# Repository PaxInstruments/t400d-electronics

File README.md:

# t400d-electronics
The T400D is the development tool based on the T400.

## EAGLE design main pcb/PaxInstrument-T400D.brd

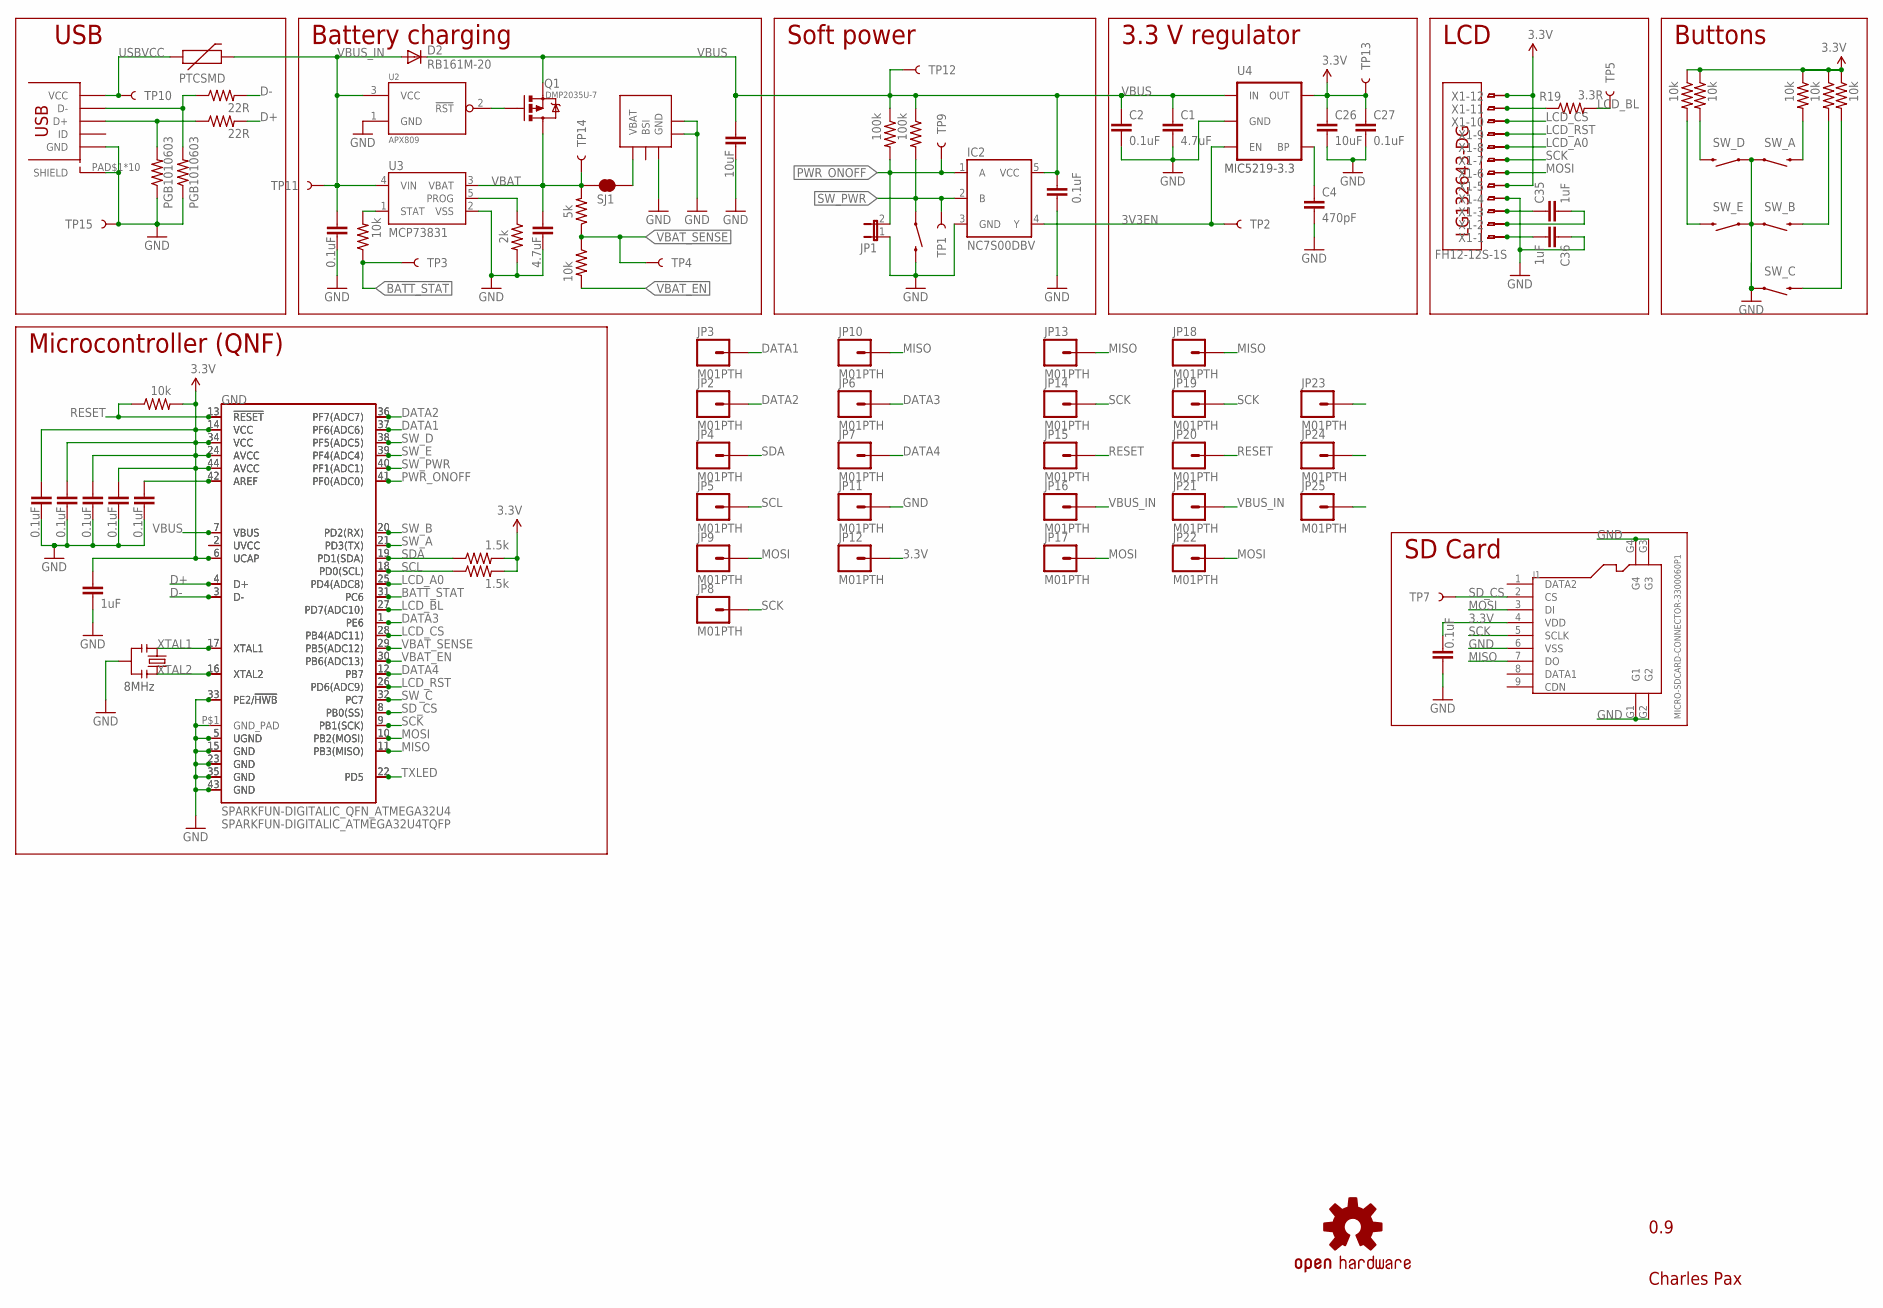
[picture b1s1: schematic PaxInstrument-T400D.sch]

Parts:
C1, C9: 4.7uF; SPARKFUN-CAPACITORS_0603-CAP; MPN GRM188R60J475KE19D
C2, C3, C5, C6, C21, C27, C28, C32, C33, C34: 0.1uF; SPARKFUN-CAPACITORS_0603-CAP; MPN CL10B104KO8NNNC
C4: 470pF; SPARKFUN-CAPACITORS_0603-CAP; MPN C1608X5R1A474K080AA
C12, C26: 10uF; SPARKFUN-CAPACITORS_0603-CAP; MPN JMK107ABJ106MAHT
C19, C35, C36: 1uF; SPARKFUN-CAPACITORS_0603-CAP; MPN LMK107B7105KA-T
D2: RB161M-20; SOD123; MPN B340A-13-F
F1: PTCSMD; PTC-1206; MPN MF-NSMF050-2
GND: SPARKFUN-DIGITALIC_QFN_ATMEGA32U4; SPARKFUN-DIGITALIC_SPARKFUN-DIGITALIC_QFN-44
IC2: NC7S00DBV; CHARLESPAX_SOT23-5
J1: MICRO-SDCARD-CONNECTOR-3300060P1; 9P-SMD-W-RING
JP1: JUMPER-2SMD-NO; SJ_2S-NO
JP2, JP3, JP4, JP5, JP6, JP7, JP8, JP9, JP10, JP11, JP12, JP13, JP14, JP15, JP16, JP17, JP18, JP19, JP20, JP21, JP22, JP23, JP24, JP25: M01PTH; 1X01
LOGO1: OSHW-LOGOS; OSHW-LOGO-S; MPN N/A
Q1: DMP2035U-7; SOT23
R3: 2k; SPARKFUN-RESISTORS_0603-RES; MPN ESR03EZPJ202
R4, R8, R11, R12, R15, R16, R17, R24: 10k; SPARKFUN-RESISTORS_0603-RES; MPN RC1608J103CS
R6, R7: 100k; SPARKFUN-RESISTORS_0603-RES; MPN RC1608J103CS
R9, R10: 22R; SPARKFUN-RESISTORS_0603-RES; MPN RC0603JR-0722RL
R13, R14: 1.5k; SPARKFUN-RESISTORS_0603-RES; MPN RC0603JR-071K5L
R19: 3.3R; SPARKFUN-RESISTORS_0603-RES
R20: 5k; SPARKFUN-RESISTORS_0603-RES; MPN RC1608J103CS
S1, S2, S3, S4, S5, S6: SWITCH-MOMENTARY-2SMD; TACTILE_SWITCH_SMD
SJ1: JUMPER-PAD-2-NC_BY_TRACE; PAD-JUMPER-2-NC_BY_TRACE_YES_SILK
TP1: SW_PWR; TP_15TH; MPN N/A
TP2: 3V3_EN; TP_15TH; MPN N/A
TP3: BATT_STAT; TP_15TH; MPN N/A
TP4: VBAT_SENSE; TP_15TH; MPN N/A
TP5: LCD_BL; TP_15TH; MPN N/A
TP7: SD_CS; TP_15TH; MPN N/A
TP9: PWR_ON/OFF; TP_15TH; MPN N/A
TP10: TEST-POINTTP_15TH_THRU; TP_15TH; MPN N/A
TP11: VBUS_IN; TP_15TH; MPN N/A
TP12: VBUS; TP_15TH; MPN N/A
TP13: 3.3V; TP_15TH; MPN N/A
TP14: VBAT; TP_15TH; MPN N/A
TP15: GND; TP_15TH
U2: APX809; SOT23
U3: MCP73831; SOT23-5; MPN MCP73831T-2DCI/OT
U4: MIC5219-3.3V; SOT23-5; MPN MIC5219-3.3YM5 TR
U$1: USB_MICROSMT+THRUHULE; USB_MICRO_THRUHOLE; MPN 10118194-0001LF
U$2: BL-5C-CONNECTOR
U$3: SPARKFUN-DIGITALIC_ATMEGA32U4TQFP; SPARKFUN-DIGITALIC_SPARKFUN-DIGITALIC_TQFP44
U$5: LG132643-DG; MPN LG132643-DW
X1: FH12-12S-1S; FH12-12S-1SH
X2: FH12-12S-0.5SH
Y1: RESONATORSMD; RESONATOR-SMD; MPN CSTCE8M00G52-R0
Z1, Z2: PGB1010603; SPARKFUN-RESISTORS_0603-RES; MPN PGB1010603NRHF

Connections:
3.3V: C5.1, C19.1, C21.2, C26.1, C27.1, C32.1, C33.1, C34.1, GND.6 (UCAP), GND.14 (VCC), GND.24 (AVCC), GND.34 (VCC), GND.44 (AVCC), J1.4 (VDD), JP12.1, R4.2, R8.1, R11.1, R12.1, R13.2, R14.2, R15.1, R16.1, TP13.P$1, U4.5 (OUT), U$3.6 (UCAP), U$3.14 (VCC), U$3.24 (AVCC), U$3.34 (VCC), U$3.44 (AVCC), X1.5, X1.12, X2.5, X2.12
3V3EN: IC2.4 (Y), TP2.P$1, U4.3 (EN)
BATT_STAT: GND.31 (PC6), R17.1, TP3.P$1, U$3.31 (PC6)
D+: GND.4 (D+), R9.2, U$3.4 (D+)
D-: GND.3 (D-), R10.2, U$3.3 (D-)
DATA1: GND.37 (PF6(ADC6)), JP3.1, U$3.37 (PF6(ADC6))
DATA2: GND.36 (PF7(ADC7)), JP2.1, U$3.36 (PF7(ADC7))
DATA3: GND.1 (PE6), JP6.1, U$3.1 (PE6)
DATA4: GND.12 (PB7), JP7.1, U$3.12 (PB7)
GND: C1.2, C2.2, C3.2, C4.2, C5.2, C6.2, C9.2, C12.2, C19.2, C21.1, C26.2, C27.2, C28.2, C32.2, C33.2, C34.2, C36.1, GND.5 (UGND), GND.15 (GND), GND.23 (GND), GND.33 (PE2/!HWB), GND.35 (GND), GND.43 (GND), GND.P$1 (GND_PAD), IC2.3 (GND), J1.6 (VSS), J1.G1, J1.G2, J1.G3, J1.G4, JP1.1, JP11.1, R3.2, S1.1, S2.1, S3.1, S4.1, S5.1, S6.3 (2), TP15.P$1, U2.1 (GND), U3.2 (VSS), U4.2 (GND), U$1.PAD$1 (SHIELD), U$1.PAD$2 (SHIELD), U$1.PAD$3 (SHIELD), U$1.PAD$4 (SHIELD), U$1.PAD$5 (SHIELD), U$1.PAD$6 (SHIELD), U$1.PAD$7 (SHIELD), U$1.PAD$8 (SHIELD), U$1.PAD$9 (SHIELD), U$1.PAD$10 (SHIELD), U$1.PIN$5 (GND), U$2.P$3 (GND), U$2.P$4, U$2.P$5, U$3.5 (UGND), U$3.15 (GND), U$3.23 (GND), U$3.33 (PE2/!HWB), U$3.35 (GND), U$3.43 (GND), X1.4, X2.4, Y1.2, Z1.1, Z2.1
LCD_A0: GND.25 (PD4(ADC8)), U$3.25 (PD4(ADC8)), X1.8, X2.8
LCD_BL: GND.27 (PD7(ADC10)), R19.2, TP5.P$1, U$3.27 (PD7(ADC10))
LCD_CS: GND.28 (PB4(ADC11)), U$3.28 (PB4(ADC11)), X1.10, X2.10
LCD_RST: GND.26 (PD6(ADC9)), U$3.26 (PD6(ADC9)), X1.9, X2.9
MISO: GND.11 (PB3(MISO)), J1.7 (DO), JP10.1, JP13.1, JP18.1, U$3.11 (PB3(MISO))
MOSI: GND.10 (PB2(MOSI)), J1.3 (DI), JP9.1, JP17.1, JP22.1, U$3.10 (PB2(MOSI)), X1.6, X2.6
MOSI2: JP25.1
unnamed: C4.1, U4.4 (BP)
unnamed: R17.2, U3.1 (STAT)
unnamed: R19.1, X1.11, X2.11
unnamed: R3.1, U3.5 (PROG)
unnamed: SJ1.2, U$2.P$1 (VBAT)
unnamed: Q1.1 (G), U2.2 (!RST)
unnamed: C3.1, GND.42 (AREF), U$3.42 (AREF)
unnamed: GND.2 (UVCC), U$3.2 (UVCC)
unnamed: R10.1, U$1.PIN$2 (D-), Z2.2
unnamed: R9.1, U$1.PIN$3 (D+), Z1.2
unnamed: C35.1, X1.3, X2.3
unnamed: C35.2, X1.2, X2.2
unnamed: C36.2, X1.1, X2.1
PWR_ONOFF: GND.41 (PF0(ADC0)), IC2.1 (A), JP1.2, R7.2, TP9.P$1, U$3.41 (PF0(ADC0))
RESET: GND.13 (!RESET), JP15.1, JP20.1, R4.1, U$3.13 (!RESET)
RESET1: JP23.1
SCK: GND.9 (PB1(SCK)), J1.5 (SCLK), JP8.1, JP14.1, JP19.1, U$3.9 (PB1(SCK)), X1.7, X2.7
SCL: GND.18 (PD0(SCL)), JP5.1, R14.1, U$3.18 (PD0(SCL))
SDA: GND.19 (PD1(SDA)), JP4.1, R13.1, U$3.19 (PD1(SDA))
SD_CS: GND.8 (PB0(SS)), J1.2 (CS), TP7.P$1, U$3.8 (PB0(SS))
SW_A: GND.21 (PD3(TX)), R8.2, S3.3 (2), U$3.21 (PD3(TX))
SW_B: GND.20 (PD2(RX)), R11.2, S2.3 (2), U$3.20 (PD2(RX))
SW_C: GND.32 (PC7), R12.2, S1.3 (2), U$3.32 (PC7)
SW_D: GND.38 (PF5(ADC5)), R15.2, S4.3 (2), U$3.38 (PF5(ADC5))
SW_E: GND.39 (PF4(ADC4)), R16.2, S5.3 (2), U$3.39 (PF4(ADC4))
SW_PWR: GND.40 (PF1(ADC1)), IC2.2 (B), R6.2, S6.1, TP1.P$1, U$3.40 (PF1(ADC1))
TXLED: GND.22 (PD5), U$3.22 (PD5)
USBVCC: F1.1, TP10.P$1, U$1.PIN$1 (VCC)
VBAT: C9.1, Q1.3 (D), R20.2, SJ1.1, TP14.P$1, U3.3 (VBAT)
VBAT_EN: GND.30 (PB6(ADC13)), R24.2, U$3.30 (PB6(ADC13))
VBAT_SENSE: GND.29 (PB5(ADC12)), R20.1, R24.1, TP4.P$1, U$3.29 (PB5(ADC12))
VBUS: C1.1, C2.1, C12.1, C28.1, D2.C, GND.7 (VBUS), IC2.5 (VCC), Q1.2 (S), R6.1, R7.1, TP12.P$1, U4.1 (IN), U$3.7 (VBUS)
VBUS_IN: C6.1, D2.A, F1.2, JP16.1, JP21.1, TP11.P$1, U2.3 (VCC), U3.4 (VIN)
VBUS_IN1: JP24.1
XTAL1: GND.17 (XTAL1), U$3.17 (XTAL1), Y1.1
XTAL2: GND.16 (XTAL2), U$3.16 (XTAL2), Y1.3

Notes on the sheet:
MIC5219-3.3
8MHz
USB
Battery charging
Soft power
3.3 V regulator
LCD
Buttons
Microcontroller (QNF)
0.9
Charles Pax
SD Card

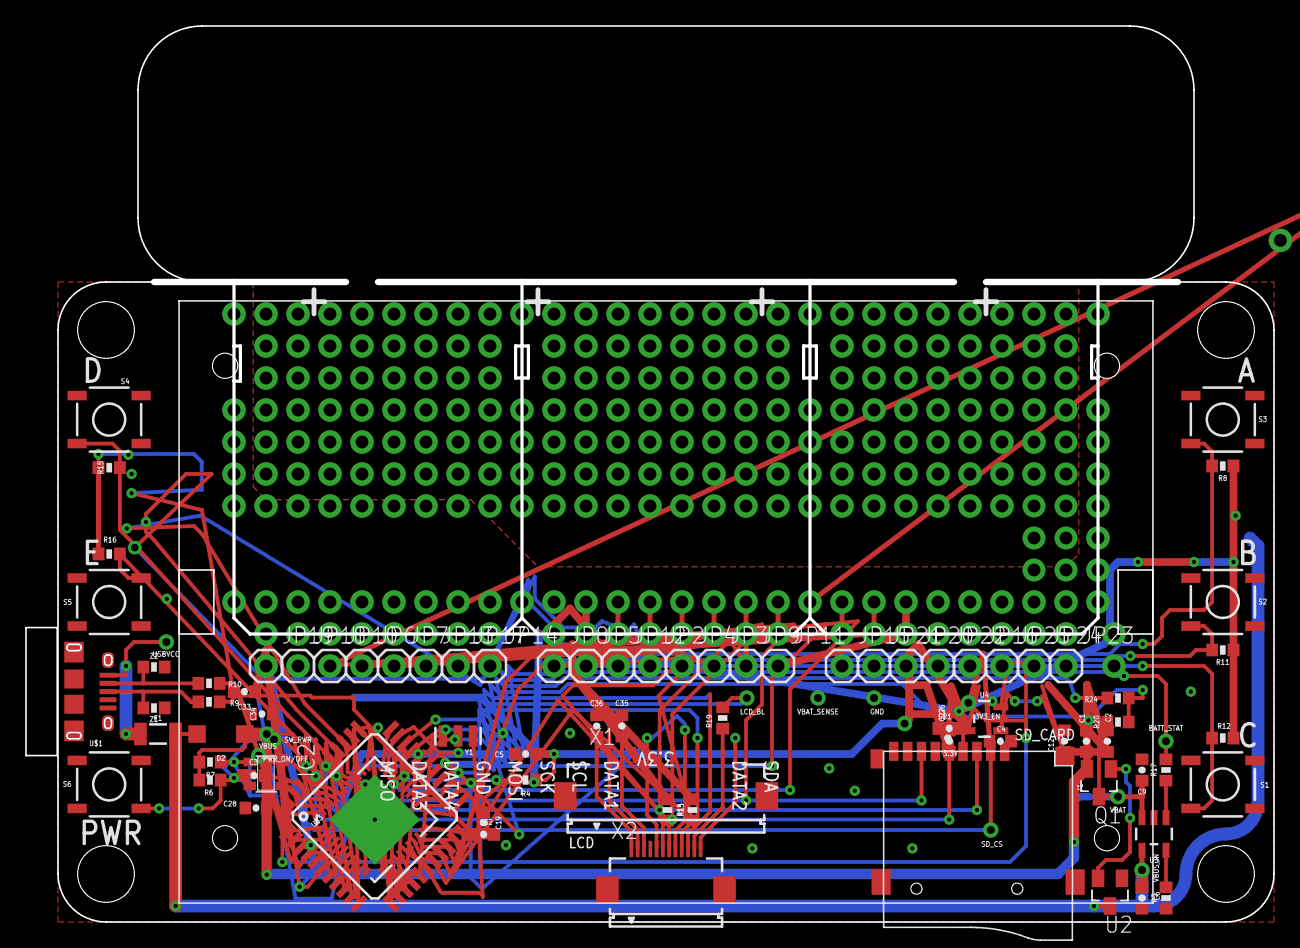
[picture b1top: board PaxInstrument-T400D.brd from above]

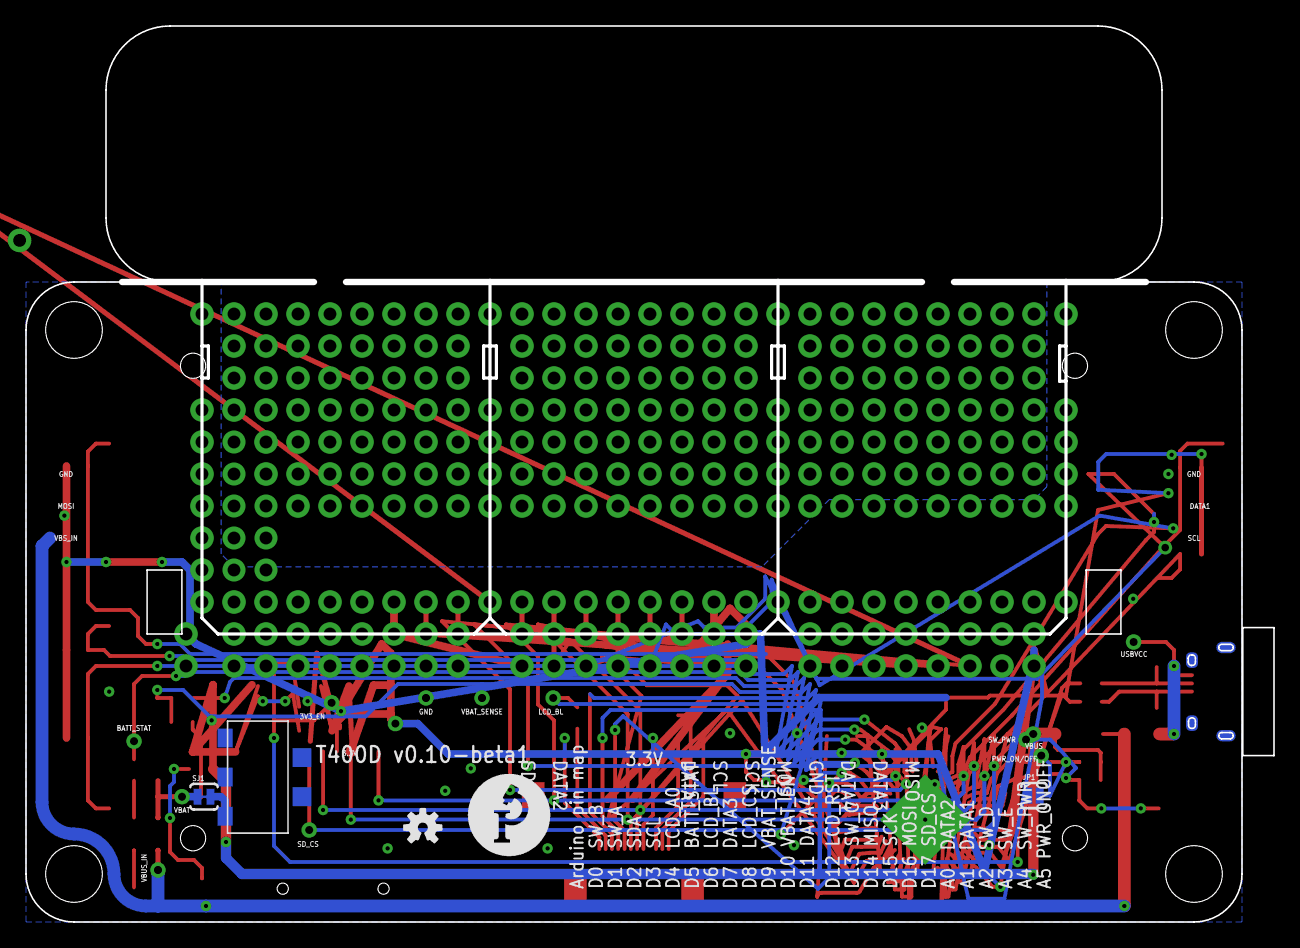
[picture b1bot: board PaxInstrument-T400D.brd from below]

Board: 2 copper layers, 98.7 x 70.7 mm, 100 parts (9 on the bottom side), 50 nets.

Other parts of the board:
U$6: PAXINSTRUMENT_LOGO

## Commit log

2015-01-27 Added insert template
2015-01-27 Added files for version 0.10 pcbs
2015-02-10 - Not sure what changed. This is still just playing around.
2015-02-20 - Moved some components to get more breakout board space. - Increased breakout board size
2015-02-27 Lengthened the modules.

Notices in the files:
parts and their libraries:
SparkFun-PowerIC: Licensing: CC v3.0 Share-Alike You are welcome to use this library for commercial purposes.
